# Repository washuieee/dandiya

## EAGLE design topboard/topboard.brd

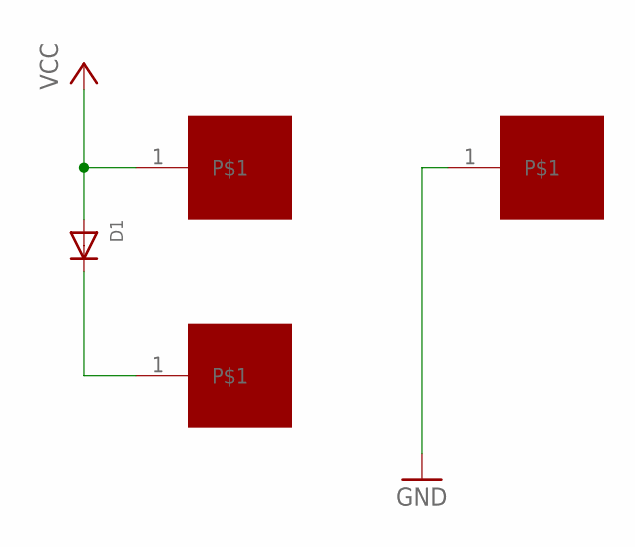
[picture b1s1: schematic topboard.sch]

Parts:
D1: DIODEDO-1N4148; DO-1N4148
P1, P2, P3: PAD

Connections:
GND: P3.1
unnamed: D1.C, P1.1
VCC: D1.A, P2.1

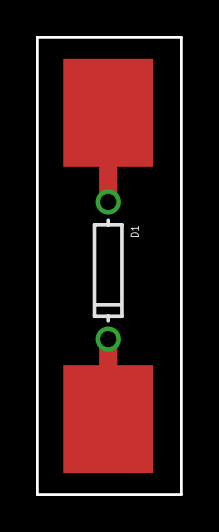
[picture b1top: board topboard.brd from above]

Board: 2 copper layers, 8.0 x 25.4 mm, 4 parts (1 on the bottom side), 2 nets.

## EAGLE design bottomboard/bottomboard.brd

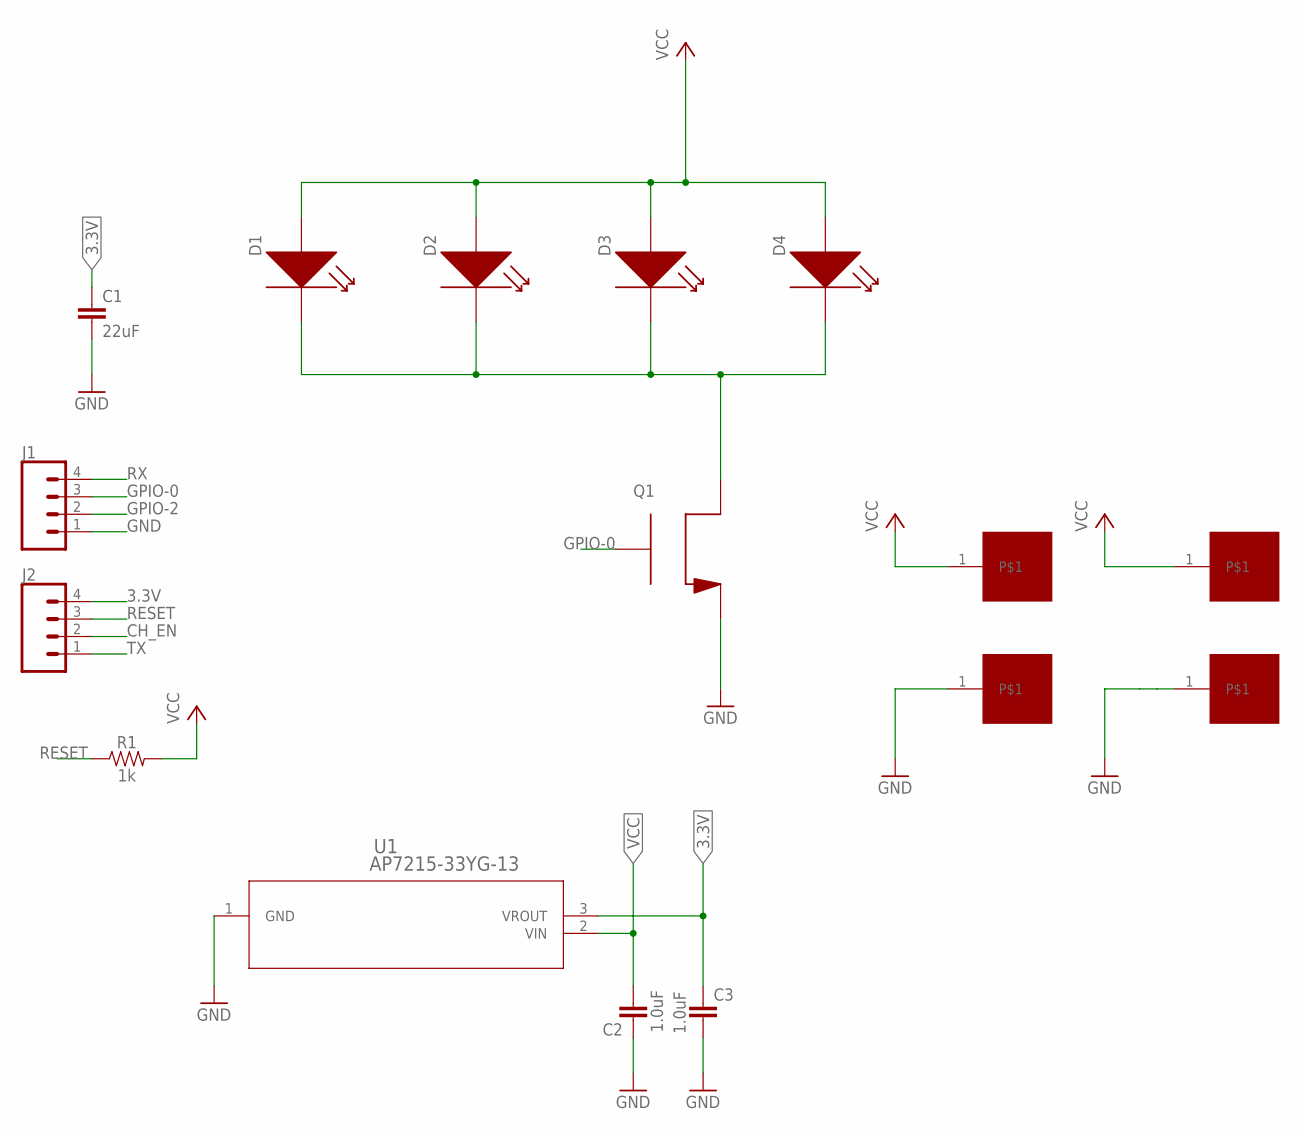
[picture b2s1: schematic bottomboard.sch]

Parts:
C1: 22uF; 0805
C2, C3: 1.0uF; 0402
D1, D2, D3, D4: NVSLE21AT
J1, J2: CONN_04; 1X04
P1, P2, P3, P4: PAD
Q1: SIA436DJ; POWERPAK_SC70-6L
R1: 1k; 0603
U1: AP7215-33YG-13; SOT89-3L

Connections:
3.3V: C1.1, C3.1, J2.4, U1.3 (VROUT)
CH_EN: J2.2
GND: C1.2, C2.1, C3.2, J1.1, P2.1, P4.1, Q1.P$2 (S), Q1.P$3 (S), U1.1 (GND)
GPIO-0: J1.3, Q1.P$4 (G)
GPIO-2: J1.2
unnamed: D1.P$1 (CATHODE), D2.P$1 (CATHODE), D3.P$1 (CATHODE), D4.P$1 (CATHODE), Q1.P$1 (D), Q1.P$5 (D), Q1.P$6 (D), Q1.P$7 (D), Q1.P$8 (D)
RESET: J2.3, R1.1
RX: J1.4
TX: J2.1
VCC: C2.2, D1.P$2 (ANODE), D2.P$2 (ANODE), D3.P$2 (ANODE), D4.P$2 (ANODE), P1.1, P3.1, R1.2, U1.2 (VIN)

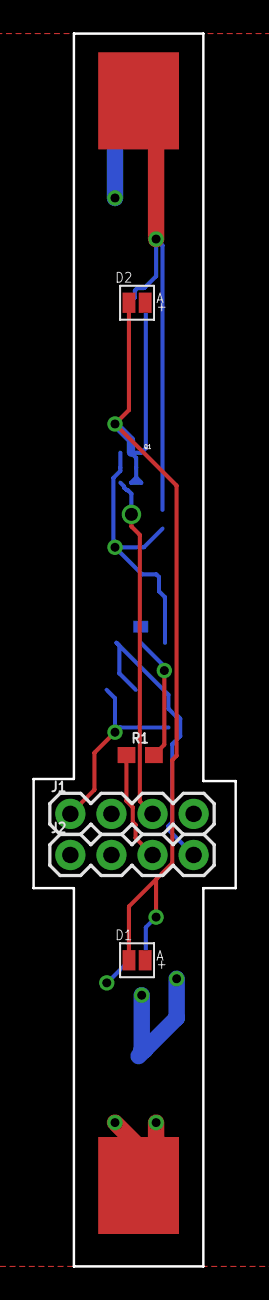
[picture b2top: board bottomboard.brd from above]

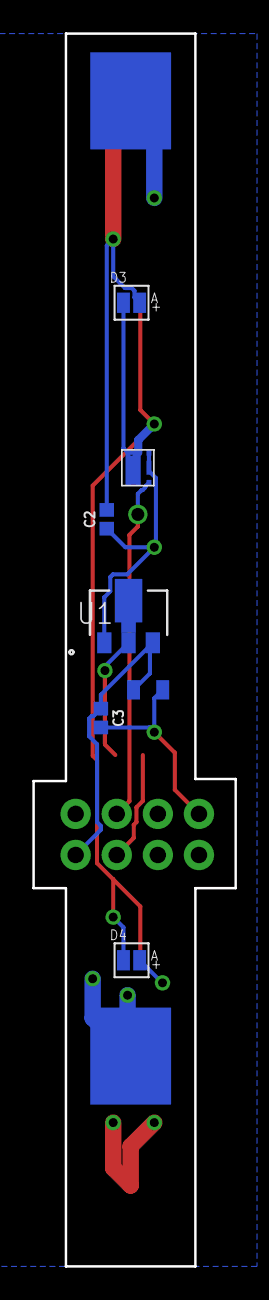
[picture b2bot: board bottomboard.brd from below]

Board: 4 copper layers, 12.5 x 76.2 mm, 16 parts (9 on the bottom side), 6 nets.

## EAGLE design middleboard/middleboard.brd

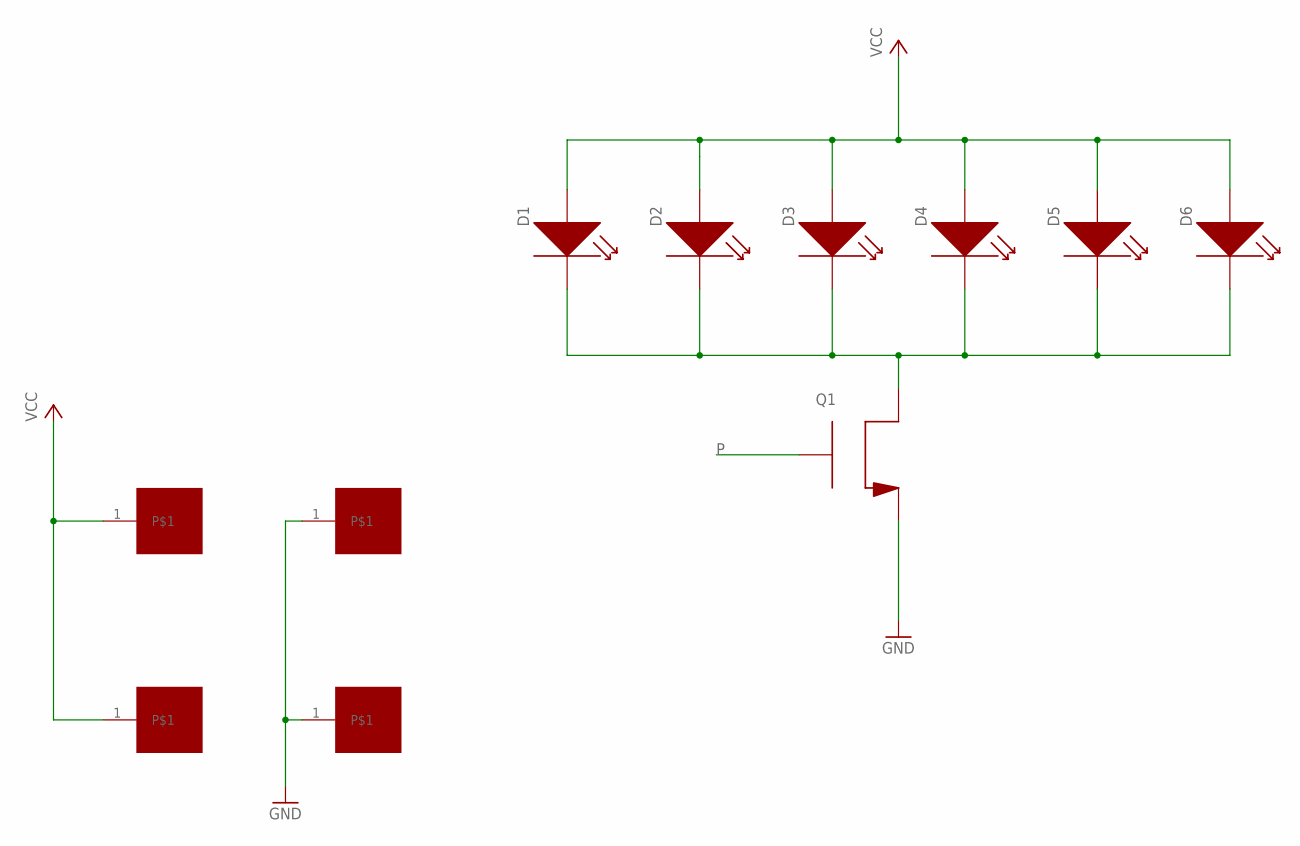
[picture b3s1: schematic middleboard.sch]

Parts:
D1, D2, D3, D4, D5, D6: NVSLE21AT
P1, P2, P3, P4: PAD
Q1: SIA436DJ; POWERPAK_SC70-6L

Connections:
GND: P2.1, P3.1, Q1.P$2 (S), Q1.P$3 (S)
unnamed: D1.P$1 (CATHODE), D2.P$1 (CATHODE), D3.P$1 (CATHODE), D4.P$1 (CATHODE), D5.P$1 (CATHODE), D6.P$1 (CATHODE), Q1.P$1 (D), Q1.P$5 (D), Q1.P$6 (D), Q1.P$7 (D), Q1.P$8 (D)
P: Q1.P$4 (G)
VCC: D1.P$2 (ANODE), D2.P$2 (ANODE), D3.P$2 (ANODE), D4.P$2 (ANODE), D5.P$2 (ANODE), D6.P$2 (ANODE), P1.1, P4.1

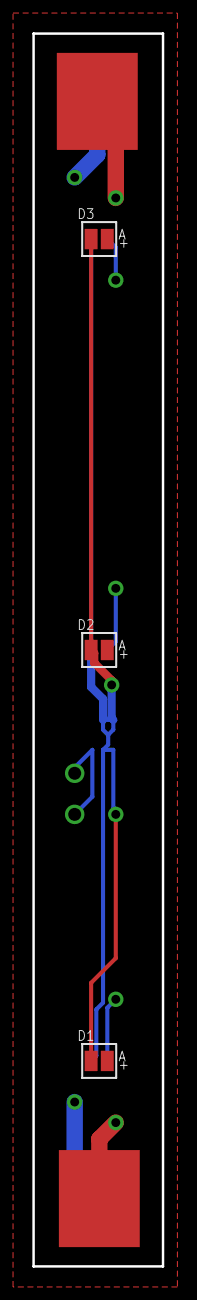
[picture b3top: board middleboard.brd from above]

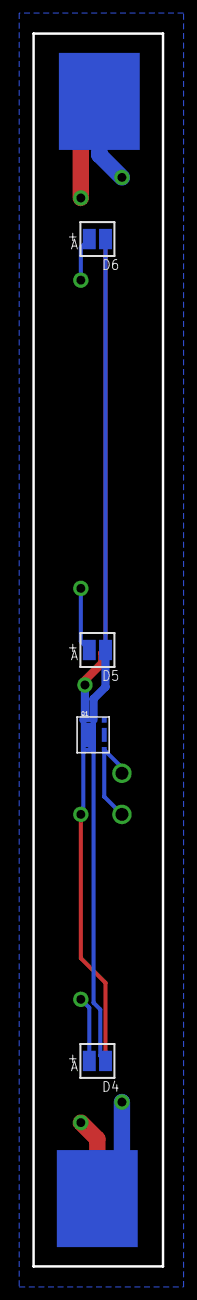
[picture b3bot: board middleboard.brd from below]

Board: 4 copper layers, 8.0 x 76.2 mm, 11 parts (6 on the bottom side), 3 nets.

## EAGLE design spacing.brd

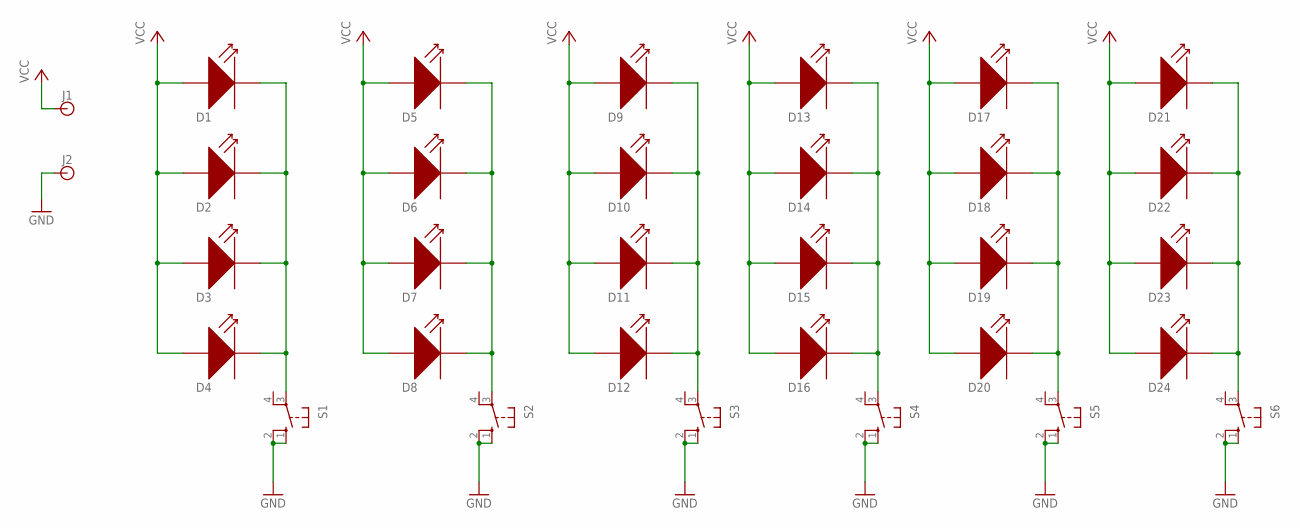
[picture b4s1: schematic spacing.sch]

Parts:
D1, D2, D3, D4, D5, D6, D7, D8, D9, D10, D11, D12, D13, D14, D15, D16, D17, D18, D19, D20, D21, D22, D23, D24: NVSLE21AT
J1, J2: BANANA_CONN
S1, S2, S3, S4, S5, S6: 10-XX; B3F-10XX

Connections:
GND: J2.P$1, S1.1 (S), S1.2 (S1), S2.1 (S), S2.2 (S1), S3.1 (S), S3.2 (S1), S4.1 (S), S4.2 (S1), S5.1 (S), S5.2 (S1), S6.1 (S), S6.2 (S1)
unnamed: D17.P$1 (CATHODE), D18.P$1 (CATHODE), D19.P$1 (CATHODE), D20.P$1 (CATHODE), S5.3
unnamed: D1.P$1 (CATHODE), D2.P$1 (CATHODE), D3.P$1 (CATHODE), D4.P$1 (CATHODE), S1.3
unnamed: D21.P$1 (CATHODE), D22.P$1 (CATHODE), D23.P$1 (CATHODE), D24.P$1 (CATHODE), S6.3
unnamed: D5.P$1 (CATHODE), D6.P$1 (CATHODE), D7.P$1 (CATHODE), D8.P$1 (CATHODE), S2.3
unnamed: D9.P$1 (CATHODE), D10.P$1 (CATHODE), D11.P$1 (CATHODE), D12.P$1 (CATHODE), S3.3
unnamed: D13.P$1 (CATHODE), D14.P$1 (CATHODE), D15.P$1 (CATHODE), D16.P$1 (CATHODE), S4.3
VCC: D1.P$2 (ANODE), D2.P$2 (ANODE), D3.P$2 (ANODE), D4.P$2 (ANODE), D5.P$2 (ANODE), D6.P$2 (ANODE), D7.P$2 (ANODE), D8.P$2 (ANODE), D9.P$2 (ANODE), D10.P$2 (ANODE), D11.P$2 (ANODE), D12.P$2 (ANODE), D13.P$2 (ANODE), D14.P$2 (ANODE), D15.P$2 (ANODE), D16.P$2 (ANODE), D17.P$2 (ANODE), D18.P$2 (ANODE), D19.P$2 (ANODE), D20.P$2 (ANODE), D21.P$2 (ANODE), D22.P$2 (ANODE), D23.P$2 (ANODE), D24.P$2 (ANODE), J1.P$1

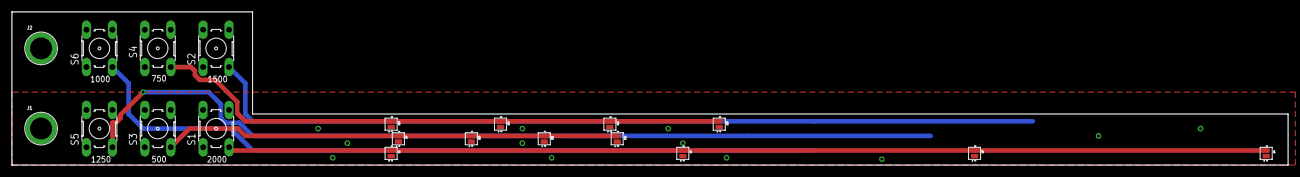
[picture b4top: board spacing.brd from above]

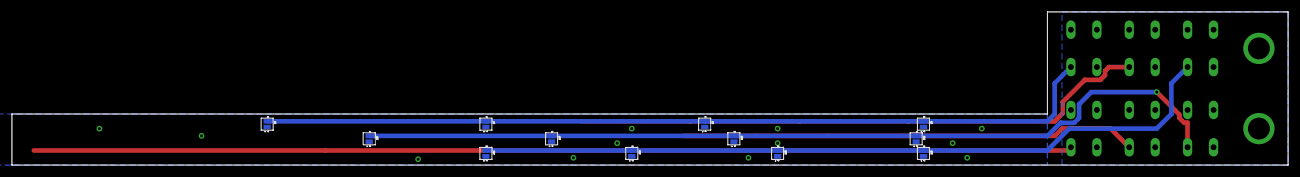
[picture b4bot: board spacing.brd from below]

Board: 2 copper layers, 222.2 x 26.7 mm, 32 parts (12 on the bottom side), 8 nets.

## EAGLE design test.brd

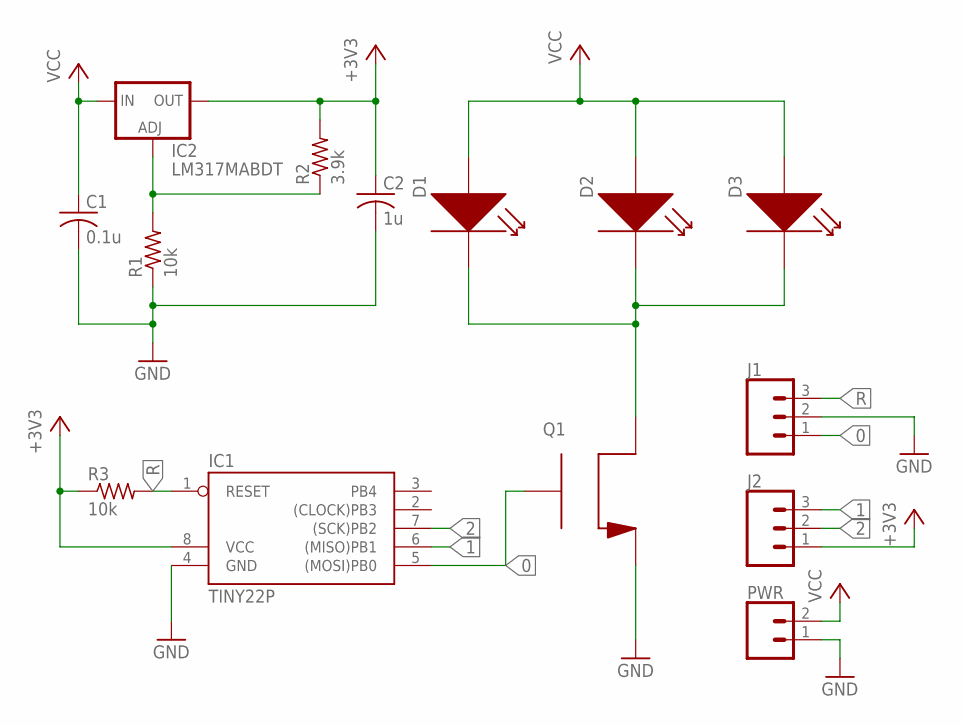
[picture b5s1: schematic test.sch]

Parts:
C1: 0.1u; C025-024X044
C2: 1u; C025-024X044
D1, D2, D3: NVSLE21AT
IC1: TINY22P; DIL08
IC2: LM317MABDT; DPACK
J1, J2: CONN_03; 1X03
PWR: CONN_02; 1X02
Q1: SIA436DJ; POWERPAK_SC70-6L
R1, R3: 10k; 0204/5
R2: 3.9k; 0204/5

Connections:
0: IC1.5 ((MOSI)PB0), J1.1, Q1.P$4 (G)
1: IC1.6 ((MISO)PB1), J2.3
2: IC1.7 ((SCK)PB2), J2.2
+3V3: C2.1, IC1.8 (VCC), IC2.4 (OUT), J2.1, R2.2, R3.1
GND: C1.2, C2.2, IC1.4 (GND), J1.2, PWR.1, Q1.P$2 (S), Q1.P$3 (S), R1.1
unnamed: D1.P$1 (CATHODE), D2.P$1 (CATHODE), D3.P$1 (CATHODE), Q1.P$1 (D), Q1.P$5 (D), Q1.P$6 (D), Q1.P$7 (D), Q1.P$8 (D)
unnamed: IC2.1 (ADJ), R1.2, R2.1
R: IC1.1 (RESET), J1.3, R3.2
VCC: C1.1, D1.P$2 (ANODE), D2.P$2 (ANODE), D3.P$2 (ANODE), IC2.3 (IN), PWR.2

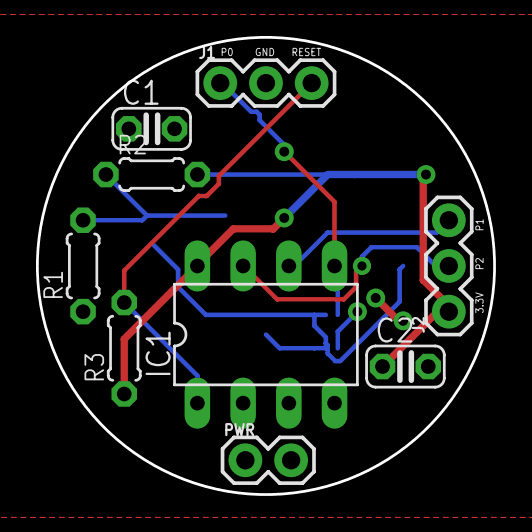
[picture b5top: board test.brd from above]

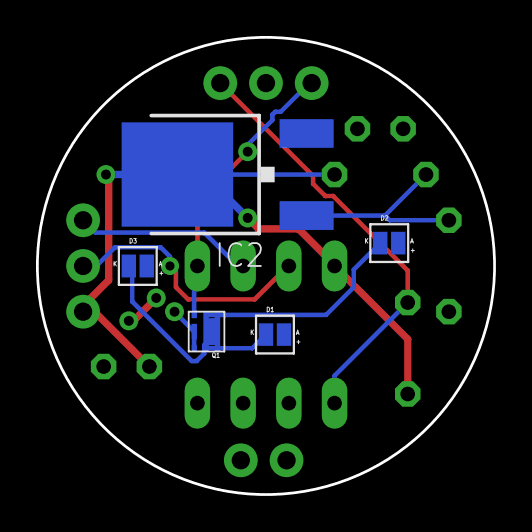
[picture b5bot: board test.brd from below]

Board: 2 copper layers, 25.4 x 25.4 mm, 14 parts (5 on the bottom side), 9 nets.

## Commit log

2019-10-18 testagain
2019-10-18 Initial bottom board design done
2019-10-18 Started on middle board
    Need to figure out how to daisy chain transistors.
2019-10-19 Increased via sizes
    Increased via sizes in bottom and
    middle boards so we can solder wires in them.
2019-10-19 First draft of top board
    Super simple, just want some method of reaching the outside
    world. Diode added for extra protection so we can't short out the
    battery from the outside.
2019-10-19 cam outputs
2019-10-24 started work on nrf receiver
2019-11-15 Work on receiver

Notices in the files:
parts and their libraries:
SparkFun-Capacitors: Licensing: Creative Commons ShareAlike 4.0 International - https://creativecommons.org/licenses/by-sa/4.0
